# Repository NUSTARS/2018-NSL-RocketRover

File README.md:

# Rocket Rover
If you are some other NSL team. Go away. 
- Please dont, we will need help

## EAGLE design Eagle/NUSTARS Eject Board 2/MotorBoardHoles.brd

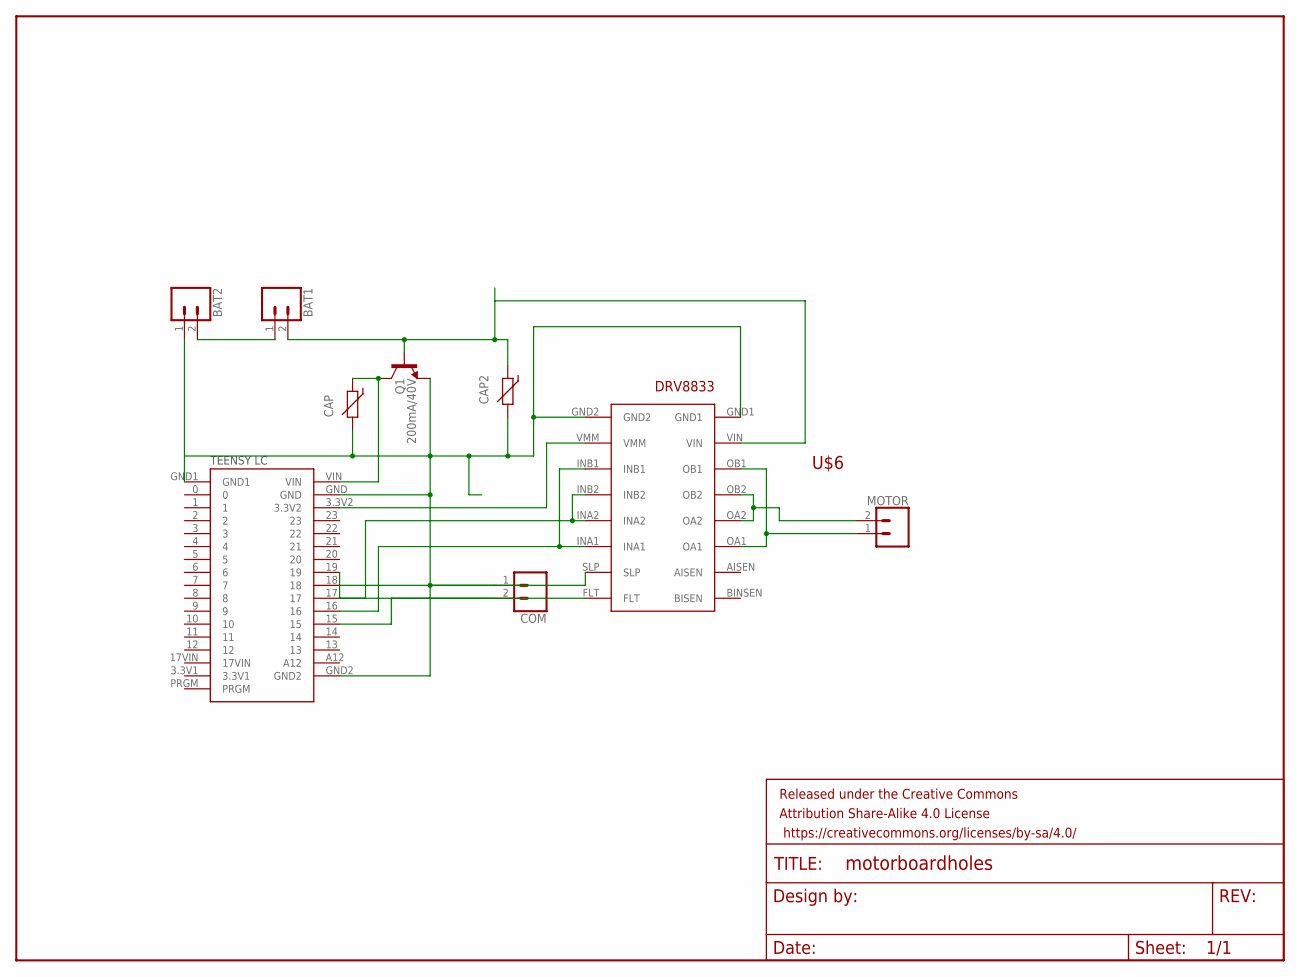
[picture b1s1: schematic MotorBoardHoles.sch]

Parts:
BAT1, BAT2: CONN_02JST-PTH-2; JST-2-PTH
CAP, CAP2: THERMISTOR_R-5; R-5
COM: CONN_02JST-PTH-2; JST-2-PTH
FRAME1: FRAME-LETTER; CREATIVE_COMMONS
MOTOR: CONN_02JST-PTH-2; JST-2-PTH
Q1: 200mA/40V; TO-92
U$1: TEENSYLC
U$6: POLOLU-DRV8833

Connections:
3.3: U$1.3.3V2, U$6.VMM
5.5V: CAP.1, Q1.3 (C), U$1.VIN
7.V4: BAT1.2, CAP2.1, Q1.2 (B), U$6.VIN
BAT_INT: BAT1.1, BAT2.2
GND: BAT2.1, CAP.2, CAP2.2, COM.1, Q1.1 (E), U$1.GND, U$1.GND1, U$1.GND2, U$6.GND1, U$6.GND2
unnamed: U$1.16, U$6.INA1, U$6.INB1
unnamed: U$1.17, U$6.INA2, U$6.INB2
unnamed: MOTOR.1, U$6.OA1, U$6.OB1
unnamed: COM.2, U$1.15
unnamed: MOTOR.2, U$6.OA2, U$6.OB2
unnamed: U$1.18, U$6.SLP
unnamed: U$1.19, U$6.FLT

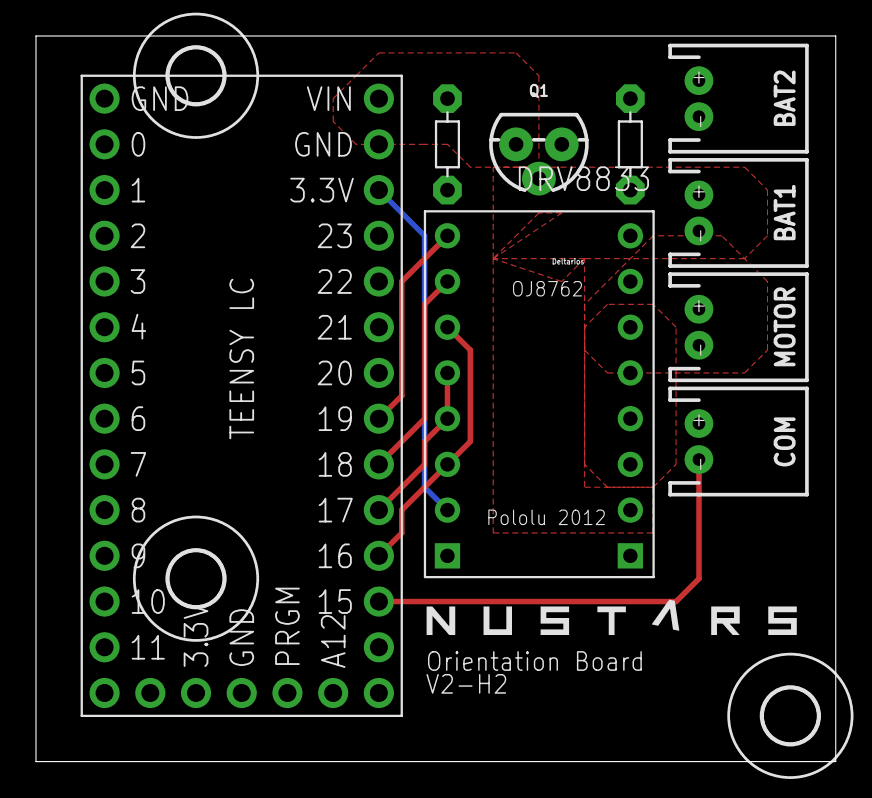
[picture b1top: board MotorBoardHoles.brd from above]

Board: 2 copper layers, 44.4 x 40.3 mm, 13 parts (0 on the bottom side), 12 nets.

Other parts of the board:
U$3, U$4, U$5: 3,0

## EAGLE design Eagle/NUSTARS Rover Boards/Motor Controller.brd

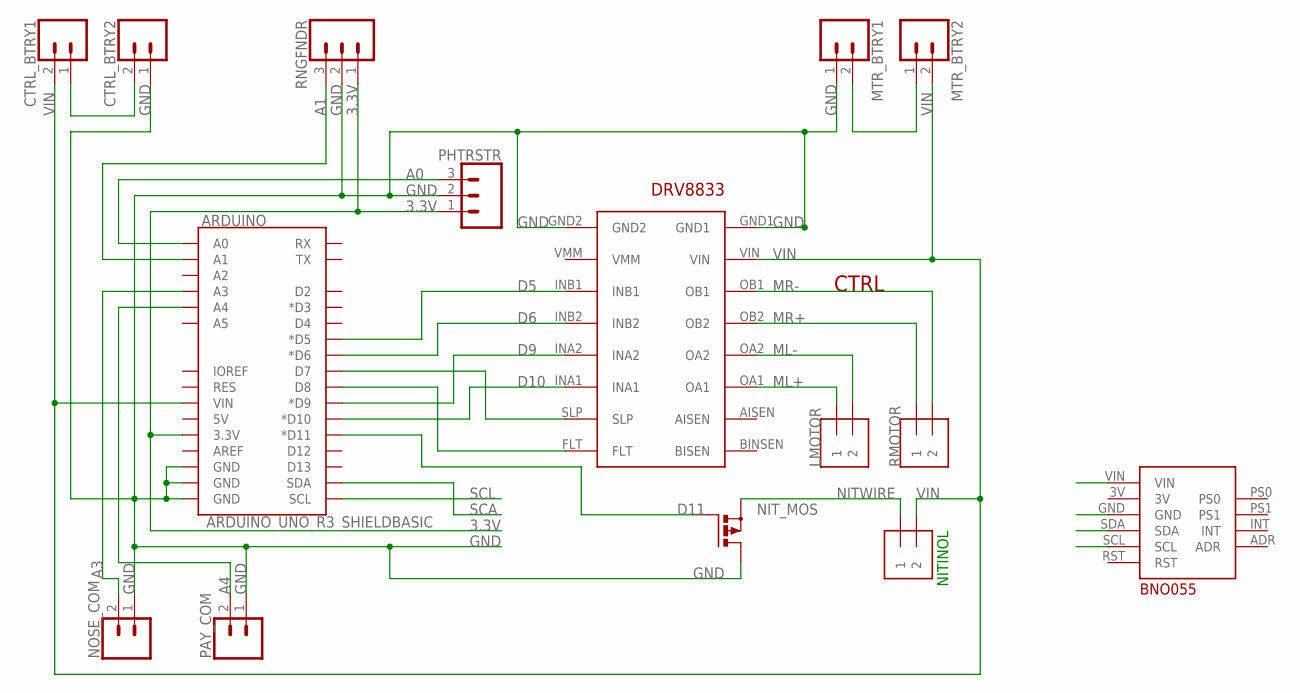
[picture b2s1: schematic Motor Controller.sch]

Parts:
ARDUINO: ARDUINO_UNO_R3_SHIELDBASIC; UNO_R3_SHIELD
CTRL: POLOLU-DRV8833
CTRL_BTRY1, CTRL_BTRY2: CONN_02-JST-2-PTH-NO_SILK; JST-2-PTH-NS
LMOTOR: 1X2-3.5MM
MTR_BTRY1, MTR_BTRY2: CONN_02-JST-2-PTH-NO_SILK; JST-2-PTH-NS
NITINOL: 1X2-3.5MM
NIT_MOS: PMOSFET_PTO220BH; TO220BH
NOSE_COM: CONN_02JST-PTH-2; JST-2-PTH
PAY_COM: CONN_02JST-PTH-2; JST-2-PTH
PHTRSTR: CONN_03JST-PTH-NS; JST-3-PTH-NS
RMOTOR: 1X2-3.5MM
RNGFNDR: CONN_03JST-PTH-NS; JST-3-PTH-NS
U$1: BNO055

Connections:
3.3V: ARDUINO.3.3V, PHTRSTR.1, RNGFNDR.1, U$1.VIN
A0: ARDUINO.A0, PHTRSTR.3
A1: ARDUINO.A1, RNGFNDR.3
A3: ARDUINO.A3, NOSE_COM.2
A4: ARDUINO.A4, PAY_COM.2
BAT_INT1: MTR_BTRY1.2, MTR_BTRY2.1
BAT_INT2: CTRL_BTRY1.1, CTRL_BTRY2.2
D5: ARDUINO.D5 (*D5), CTRL.INB1
D6: ARDUINO.D6 (*D6), CTRL.INB2
D9: ARDUINO.D9 (*D9), CTRL.INA2
D10: ARDUINO.D10 (*D10), CTRL.INA1
D11: ARDUINO.D11 (*D11), NIT_MOS.G
GND: ARDUINO.GND@0 (GND), ARDUINO.GND@1 (GND), ARDUINO.GND@2 (GND), CTRL.GND1, CTRL.GND2, CTRL_BTRY2.1, MTR_BTRY1.1, NIT_MOS.D, NOSE_COM.1, PAY_COM.1, PHTRSTR.2, RNGFNDR.2, U$1.GND
ML+: CTRL.OA1, LMOTOR.1
ML-: CTRL.OA2, LMOTOR.2
MR+: CTRL.OB2, RMOTOR.1
MR-: CTRL.OB1, RMOTOR.2
unnamed: ARDUINO.D7, CTRL.SLP
unnamed: ARDUINO.D8, CTRL.FLT
NITWIRE: NITINOL.1, NIT_MOS.S
SCA: ARDUINO.SDA, U$1.SDA
SCL: ARDUINO.SCL, U$1.SCL
VIN: ARDUINO.VIN, CTRL.VIN, CTRL_BTRY1.2, MTR_BTRY2.2, NITINOL.2

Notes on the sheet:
NITINOL
LMOTOR
RMOTOR

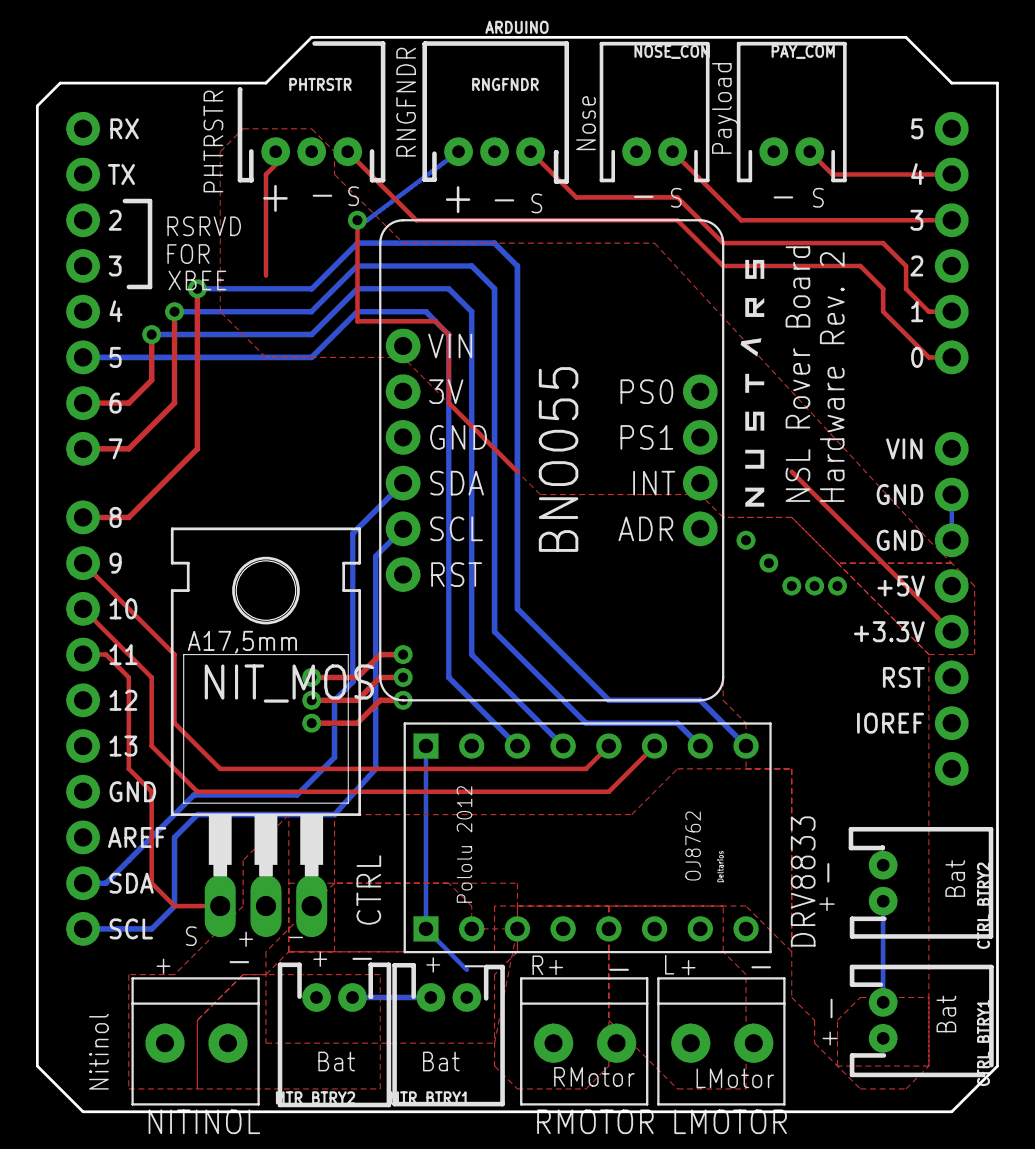
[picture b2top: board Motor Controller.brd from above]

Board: 2 copper layers, 53.3 x 59.7 mm, 15 parts (0 on the bottom side), 23 nets.

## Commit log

2018-02-04 wheel controls
2018-02-04 Ethan doesn't know the difference bt break and brake
2018-02-08 xbee stuff, and Werblin is a dumbass
2018-02-15 nose cone code
2018-02-15 made some small fixes
2018-02-18 tiny bug fix
2018-02-18 made bug fixes
2018-02-21 changes for ichi
2018-02-21 Add hold status. Add button interrupt. Add LED indictors. Button short to ground triggers mode change.
2018-03-01 Add eagle files
2018-03-11 rover Xbee control .ino file
2018-03-15 movement
2018-03-29 Add Rover test files
2018-03-29 Reduce Rover Speed
2018-03-29 Revert to basic testing
2018-03-29 minor bugfix
2018-03-29 delay for install
2018-03-29 forwards back loop
2018-03-29 Revert to working
2018-03-29 Multistage trigger added
2018-03-29 rename files. implement two stage trigger
2018-03-29 change speed
2018-03-29 Revert to forwards only. hard code pins.
2018-03-30 bugfix trigger stage 2
2018-03-30 bug fix direction oscillator
2018-04-01 xbee test
2018-04-02 Add rover
2018-04-06 New Rover Movement Code, now in "RoverTestNew"
2018-04-06 roverTestNew Updates
2018-04-06 more changes to rover movement code

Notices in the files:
parts and their libraries:
SparkFun-Aesthetics: Licensing: Creative Commons ShareAlike 4.0 International - https://creativecommons.org/licenses/by-sa/4.0
SparkFun-Aesthetics: Released under the Creative Commons Attribution Share-Alike 4.0 License
SparkFun-Aesthetics: https://creativecommons.org/licenses/by-sa/4.0
